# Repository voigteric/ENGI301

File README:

ENGI301
Description: Repository for ENGI301 course work

assignment_05 -- homework submission for assignment_05
project_01 -- instrument glove (embedded systems and hardware)
project_02 -- instrument glove printed circuit board (EAGLE board, schematic, and library; manufacturing outputs; general documentation)

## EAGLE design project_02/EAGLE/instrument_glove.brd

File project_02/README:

INSTRUMENT GLOVE PRINTED CIRCUIT BOARD
by ERIC VOIGT

A printed circuit board and manufacturing information for the instrument glove project (project_01)
Please visit https://www.hackster.io/eric-voigt/instrument-glove-4537b7 for a complete tutorial and build instructions.

IMPLEMENTATION FILES:
instrument_glove.lbr -- EAGLE library containing instrument glove components
instrument_glove.brd -- EAGLE board (layout for project)
instrument_glove.sch -- EAGLE schematic

MANUFACTURING FILES:
DRU & CAM files used in Eagle for layout
Gerber & other mfg output files located in "gerber & output files" -- select by file type for a particular viewer

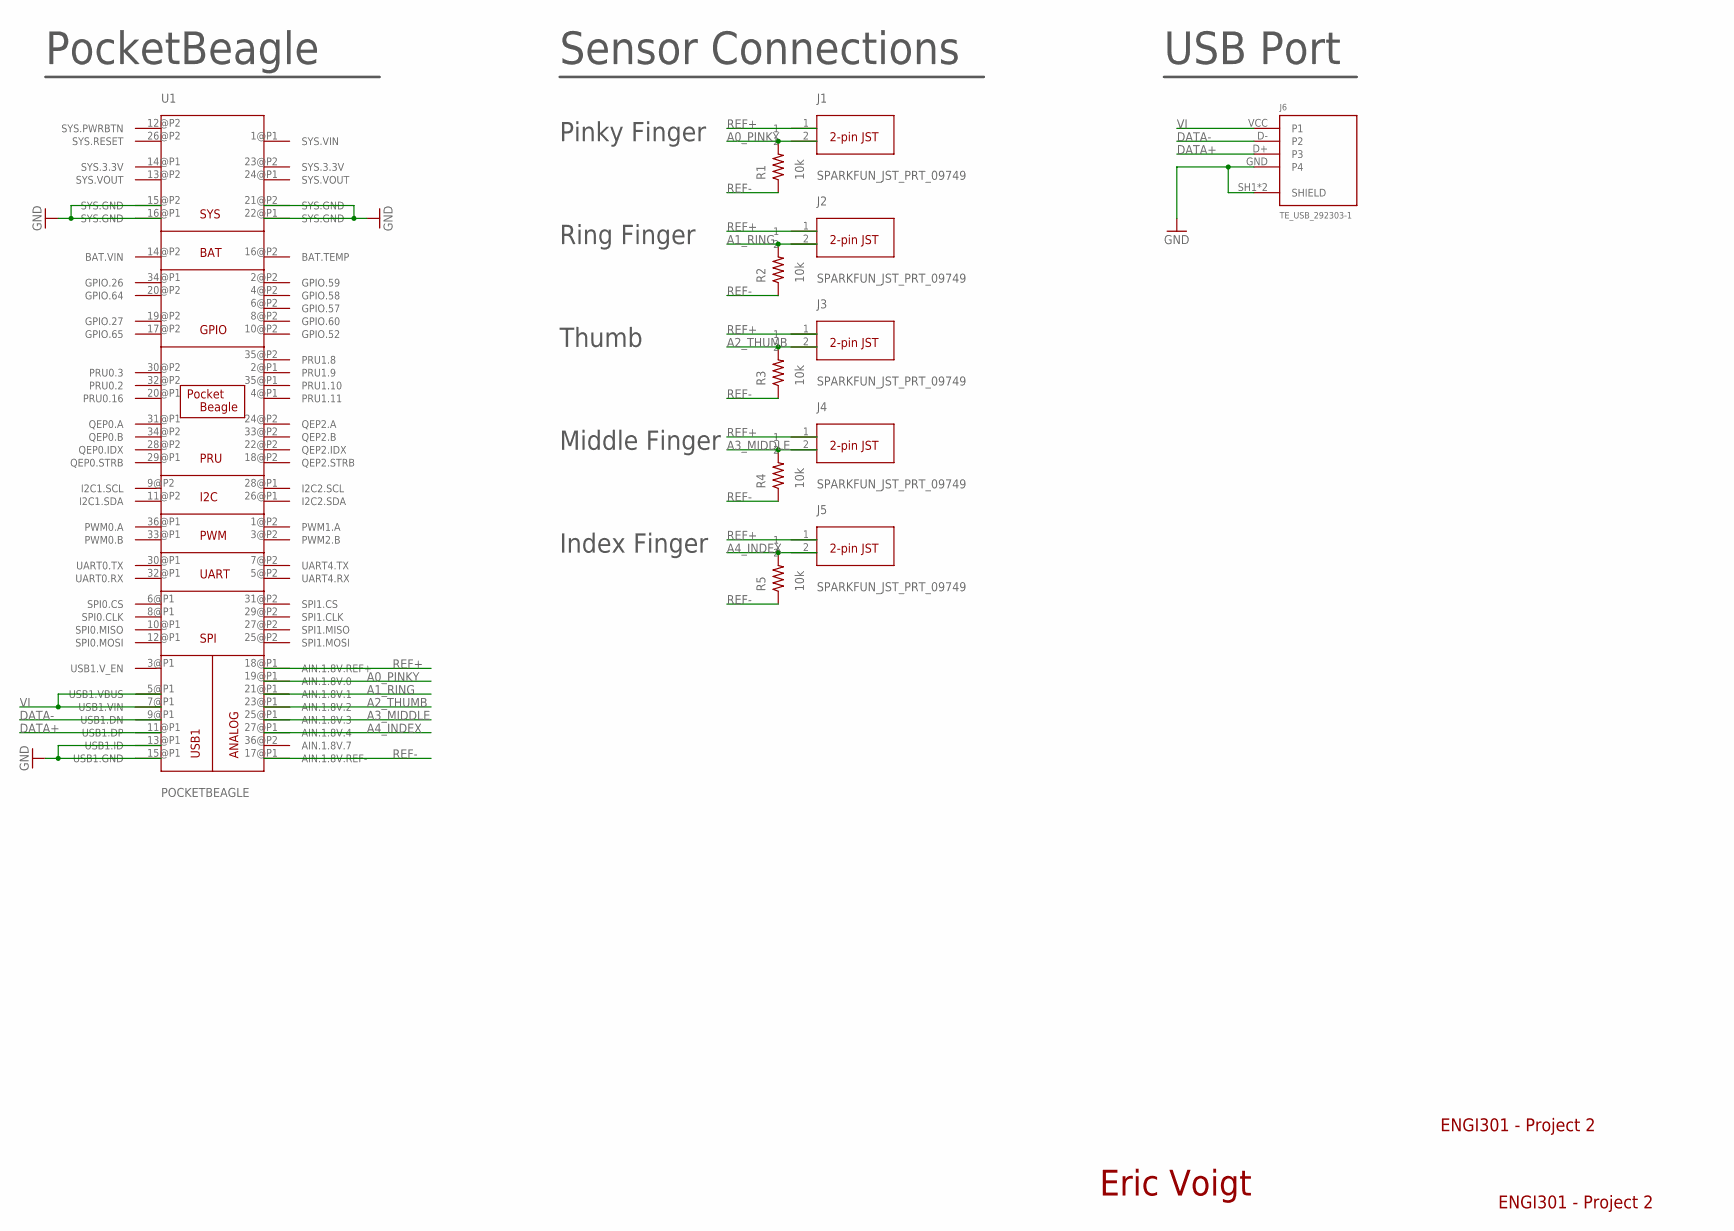
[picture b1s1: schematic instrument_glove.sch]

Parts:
J1, J2, J3, J4, J5: SPARKFUN_JST_PRT_09749
J6: TE_USB_292303-1
R1, R2, R3, R4, R5: 10k; R0603
U1: POCKETBEAGLE

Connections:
A0_PINKY: J1.2, R1.2, U1.19@P1 (AIN.1.8V.0)
A1_RING: J2.2, R2.2, U1.21@P1 (AIN.1.8V.1)
A2_THUMB: J3.2, R3.2, U1.23@P1 (AIN.1.8V.2)
A3_MIDDLE: J4.2, R4.2, U1.25@P1 (AIN.1.8V.3)
A4_INDEX: J5.2, R5.2, U1.27@P1 (AIN.1.8V.4)
DATA+: J6.D+ (P3), U1.11@P1 (USB1.DP)
DATA-: J6.D- (P2), U1.9@P1 (USB1.DN)
GND: J6.GND (P4), J6.SH1 (SHIELD), J6.SH2 (SHIELD), U1.13@P1 (USB1.ID), U1.15@P1 (USB1.GND), U1.15@P2 (SYS.GND), U1.16@P1 (SYS.GND), U1.21@P2 (SYS.GND), U1.22@P1 (SYS.GND)
REF+: J1.1, J2.1, J3.1, J4.1, J5.1, U1.18@P1 (AIN.1.8V.REF+)
REF-: R1.1, R2.1, R3.1, R4.1, R5.1, U1.17@P1 (AIN.1.8V.REF-)
SYS.3.3V: U1.14@P1 (SYS.3.3V), U1.23@P2 (SYS.3.3V)
SYS.PWRBTN: U1.12@P2 (SYS.PWRBTN)
SYS.RESET: U1.26@P2 (SYS.RESET)
VI: J6.VCC (P1), U1.5@P1 (USB1.VBUS), U1.7@P1 (USB1.VIN)

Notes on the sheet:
PocketBeagle
Sensor Connections
USB Port
ENGI301 - Project 2
Eric Voigt
Pinky Finger
Ring Finger
Thumb
Middle Finger
Index Finger

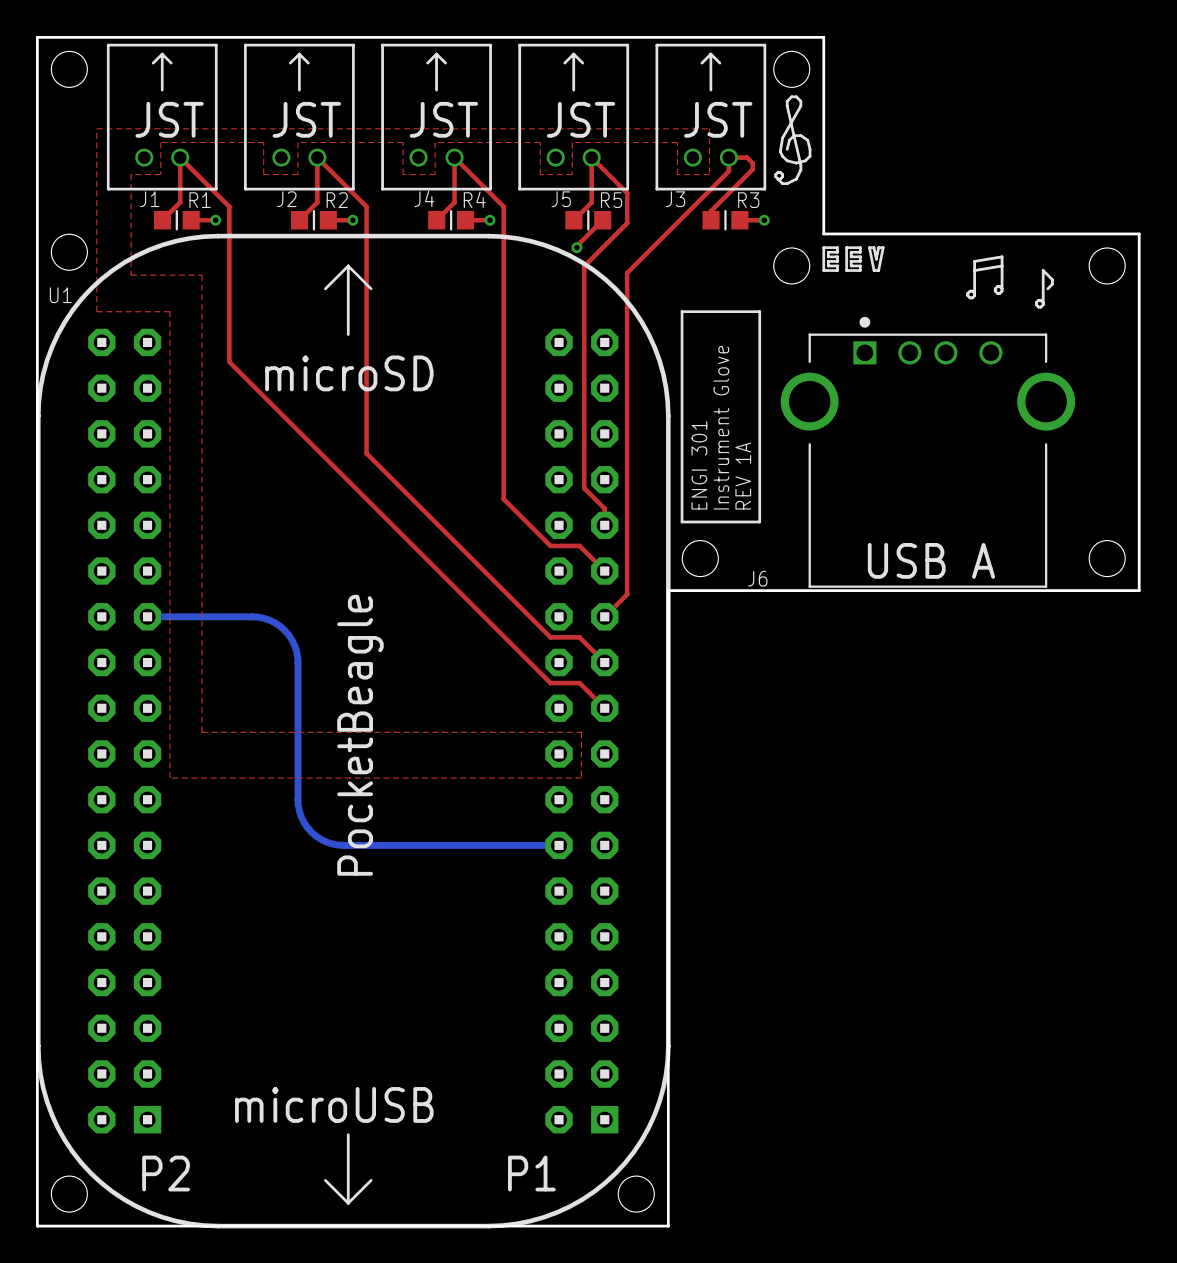
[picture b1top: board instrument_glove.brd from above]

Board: 4 copper layers, 61.2 x 66.0 mm, 12 parts (0 on the bottom side), 12 nets.

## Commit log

2019-09-18 Updating README.md
2019-10-06 Assignment #5: Problem 1, Part b
2019-10-06 Renamed file
2019-10-06 Final simple calc
2019-10-07 Program to blink USR3 LED at 5Hz
2019-10-23 adding proposals
2019-10-29 general project work update
2019-10-30 project work update
2019-11-06 again revised project proposal to include drums
2019-11-13 assembling final documentation for project
2019-11-13 change directory name
2019-11-15 add runtime script
2019-11-15 update startup script
2019-11-15 Rename README.md to README
2019-11-25 files update
2019-12-15 project_02 submission
2019-12-15 update library
2019-12-15 project_02 submission updates
